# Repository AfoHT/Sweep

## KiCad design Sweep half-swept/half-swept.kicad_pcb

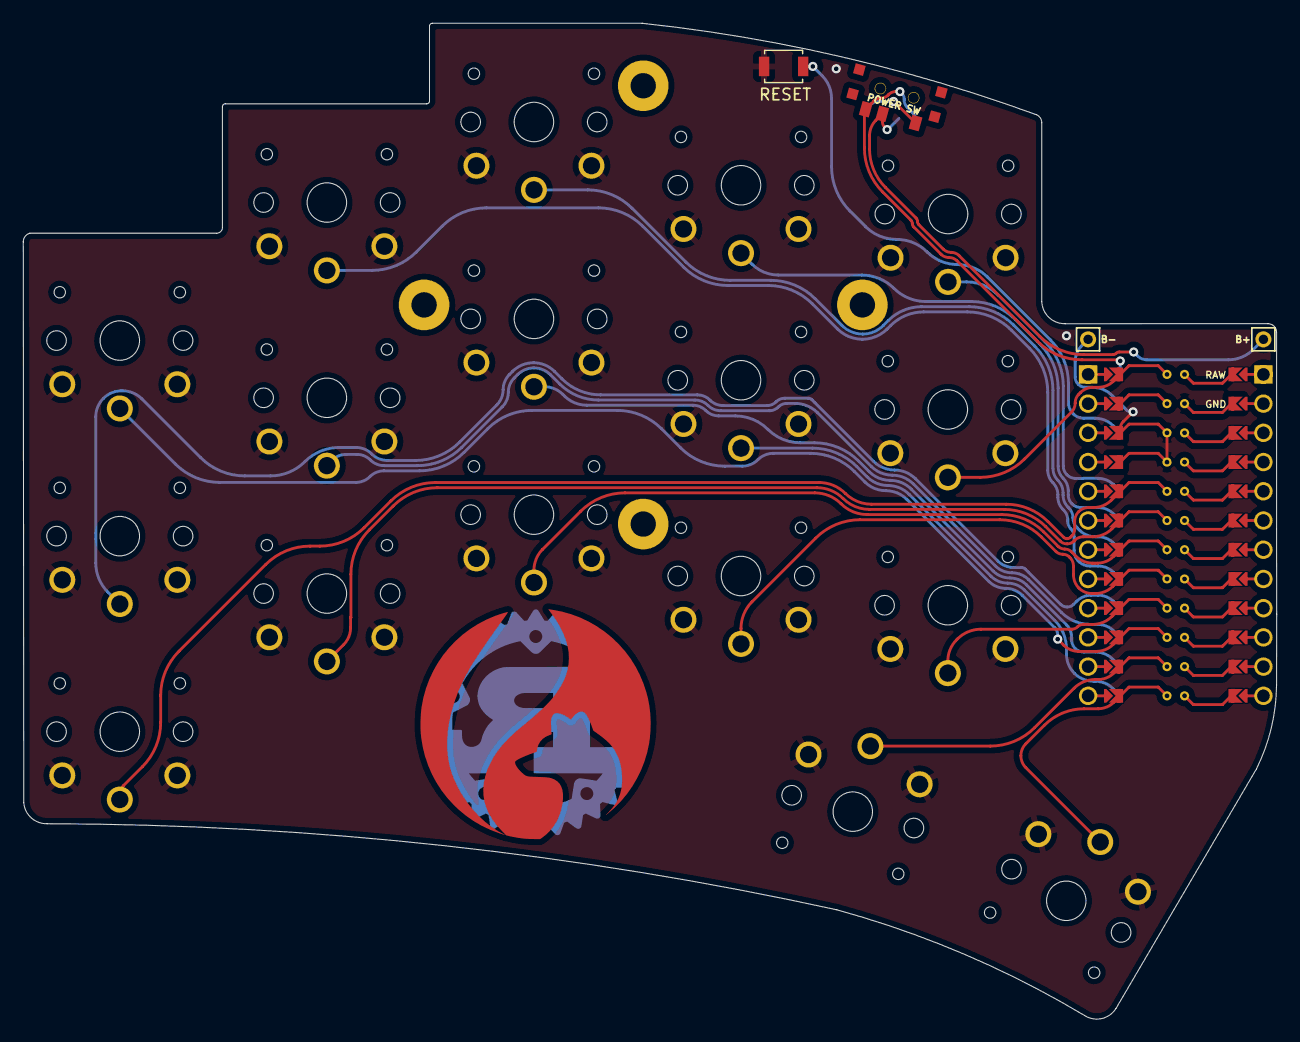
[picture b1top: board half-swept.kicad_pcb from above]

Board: 2 copper layers, 109.0 x 86.6 mm, 22 parts (0 on the bottom side), 21 nets.

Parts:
B+: MountingHole_Pad; 1pin_conn
B-: MountingHole_Pad; 1pin_conn
POWER SW: SW_SPDT; SPDT_C128955
RSW2: SW_Push; Tactile-Switch_SMT
SW1, SW2, SW3, SW4, SW5, SW6, SW7, SW8, SW9, SW10, SW11, SW12, SW13, SW14, SW15, SW16, SW17: SW_Push; SW_PG1350_rev_DPB
U1: ProMicro-kbd; ProMicro_jumpers_facedown

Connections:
BT+_r: B+.1, POWER SW.2
Switch1: SW1.1, U1.10
Switch2: SW2.1, U1.17
Switch3: SW3.1, U1.18
Switch4: SW4.1, U1.19
Switch5: SW5.1, U1.20
Switch6: SW6.1, U1.16
Switch7: SW7.1, U1.15
Switch8: SW8.1, U1.14
Switch9: SW9.1, U1.13
Switch10: SW10.1, U1.1
Switch11: SW11.1, U1.5
Switch12: SW12.1, U1.6
Switch13: SW13.1, U1.7
Switch14: SW14.1, U1.8
Switch15: SW15.1, U1.9
Switch16: SW16.1, U1.11
Switch17: SW17.1, U1.12
gnd: B-.1, RSW2.1, RSW2.2, SW1.2, SW2.2, SW3.2, SW4.2, SW5.2, SW6.2, SW7.2, SW8.2, SW9.2, SW10.2, SW11.2, SW12.2, SW13.2, SW14.2, SW15.2, SW16.2, SW17.2, U1.3, U1.4, U1.23
raw: POWER SW.3, U1.24
reset: RSW2.1, RSW2.2, U1.22

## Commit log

2022-12-09 Save old work before rebase
2022-12-09 Remove Half Swept silkscreen
2022-12-09 Make PCB follow switch outline instead of arc
2022-12-09 Save PG1350 library
2022-12-09 Switch to local PG1350 lib
2022-12-09 Hide Tenting puck F.Fab text
2022-12-09 Remove right-angle silkscreen
2022-12-11 Some modifications?
2022-12-11 Remove Tenting-puck lines/artwork
2022-12-11 Add RTIC logo
2022-12-11 Cleanup TRRS and add Rust logo
2022-12-11 Added kicad_mods for artwork
2022-12-11 Round tracks plugin
2022-12-11 Add copper layer to RTIC logo
2022-12-11 Fix logos
2022-12-11 Remove bounding box for MCU
2022-12-11 Remove assembly instructions from silkscreen
2022-12-11 Remove TRRS
2022-12-11 Move Rust logo, make it larger
2022-12-11 Also fill all zones
